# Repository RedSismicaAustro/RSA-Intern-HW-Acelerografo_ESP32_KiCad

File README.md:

# 🚀 Rediseño y Estandarización de PCB Acelerográfica en KiCad 10 (PCBA JLCPCB)

Este repositorio contiene el espacio de trabajo, documentación de referencia y material de apoyo para el desarrollo de la pasantía de **Joel Suárez** en la **Red Sísmica del Austro (RSA)**.

El objetivo central es capturar, auditar, optimizar y estandarizar el diseño del **Sistema Acelerográfico con ESP32 (SMD)** en el entorno **KiCad 10**, garantizando que el diseño sea 100% compatible con el firmware de adquisición original y esté preparado para ensamblaje automático (**PCBA**) en **JLCPCB**.

---

## 📂 Organización del Repositorio

Para mantener el flujo de trabajo simple y ordenado, el proyecto está estructurado en tres carpetas:

```text
RSA-Intern-HW-Acelerografo_ESP32_KiCad/
│
├── .gitignore                                 # Configurado para ignorar temporales y respaldos de KiCad
├── README.md                                  # Guía operativa e instrucciones de trabajo
│
├── docs/                                      # Documentación técnica de apoyo y planificación
│   ├── Planificacion_Migracion_EAGLE_KiCad.pdf # Plan de trabajo oficial detallado (96 horas)
│   └── especificacion_hardware_original.md    # Detalle de circuitos integrados, valores pasivos y pines
│
├── eagle/                                     # Material de referencia del diseño previo
│   ├── BOM_Assembly.txt                       # Lista de materiales (BOM) con valores, referencias y encapsulados
│   ├── images_schematic/                      # Capturas de los esquemas por bloques (Páginas 1 a 7 y Full)
│   └── images_pcb_3d_view/                    # Vistas 3D de referencia de la placa previa
│
└── kicad/                                     # 👉 Espacio de trabajo exclusivo para el nuevo proyecto KiCad 10
```

---

## 🧭 Metodología de Trabajo y Fases (96 horas)

Dado que el diseño previo proviene de una versión en Autodesk Fusion Electronics / EAGLE sin archivos de proyecto nativos disponibles, el trabajo se desarrollará directamente en **KiCad 10** en la carpeta [`kicad/`](./kicad) siguiendo estas 6 fases:

### 1. Captura de Esquemático y Auditoría de Pines (Pinout Audit - 16 h)
* **Captura en KiCad 10:** Crear el proyecto en [`kicad/`](./kicad) y dibujar los bloques esquemáticos utilizando como referencia las capturas en [`eagle/images_schematic/`](./eagle/images_schematic), la lista de materiales en [`eagle/BOM_Assembly.txt`](./eagle/BOM_Assembly.txt) y la [`especificacion_hardware_original.md`](./docs/especificacion_hardware_original.md).
* **Auditoría estricta contra Firmware:** Cotejar pin a pin la asignación de GPIOs del ESP32 con el código fuente del firmware de adquisición disponible en [RSA Sensor (GitHub)](https://github.com/JorgeZh-hub/RSA_sensor):
  * **ADXL355Z (SPI):** `MOSI`, `MISO`, `SCK`, `CS`.
  * **Tarjeta MicroSD (SPI + Buffer 74LVC125A):** `MOSI`, `MISO`, `SCK`, `CS`.
  * **GPS (UART):** `TX`, `RX`.
  * **RTC DS3231 (I2C + SQW):** `SDA`, `SCL`, interrupción `SQW` (1 Hz).
  * **Conversor USB/Serial (UART):** `TXD0`, `RXD0`, `DTR`, `RTS` hacia el CH340G.

### 2. Estandarización de Componentes y Códigos LCSC (16 h)
* Asignar a cada símbolo el campo de metadatos `LCSC` con el número de parte (*LCSC Part Number*) del catálogo de JLCPCB.
* Priorizar componentes clasificados como **Basic Parts** de JLCPCB para reducir costos de montaje.
* Seleccionar encapsulados SMD estándar adecuados (0805, 0603, 1206, SOT-23, SOIC).

### 3. Gestión de Librerías Locales Relativas (12 h)
* Utilizar la herramienta `jlc2kicadlib` para descargar componentes específicos que no estén en la librería oficial de KiCad.
* Alojar todos los símbolos (`.kicad_sym`), huellas (`.kicad_mod` en carpeta `.pretty`) y modelos 3D (`.step`) dentro de carpetas locales del proyecto (ej. `kicad/libs/`).
* Configurar las rutas mediante variables relativas del entorno KiCad (ej. `${KIPRJMOD}`) para que el repositorio sea **100% portable y autónomo** al clonarse en cualquier computador.

### 4. Layout Físico, Integridad y Optimización (24 h)
* **Desacoplo:** Ubicar condensadores de desacoplo (0.1 µF y 10 µF) lo más próximos posible a los pines `VCC`/`VDD` del ESP32, ADXL355 y RTC.
* **Plano de Masa:** Implementar planos de tierra robustos de cobre (GND) en ambas capas (Top y Bottom).
* **Señales Críticas:** Rutar con trazas cortas y directas las líneas de datos SPI del acelerómetro y MicroSD, minimizando el número de vías.
* **Test Points:** Incluir puntos de prueba accesibles (pads/headers) para señales críticas (`3.3V`, `5V`, `GND`, `TX/RX`, `SQW 1Hz`, bus SPI).
* **Pick & Place:** Colocar al menos 3 marcas fiduciarias (*Fiducials*) en las esquinas de la PCB.
* **DRC:** Ejecutar el Design Rules Check de KiCad y asegurar 0 errores/advertencias.

### 5. Generación y Validación de Archivos de Fabricación (14 h)
* Instalar y utilizar el plugin **Fabrication Toolkit** en KiCad para generar automáticamente el paquete PCBA:
  * Archivos Gerber y NC Drill.
  * Lista de Materiales (`BOM.csv`).
  * Archivo de Posición y Coordenadas (`CPL.csv`).
* Cargar el paquete en el visor web de JLCPCB para auditar y corregir rotaciones u offsets de los componentes SMD.

### 6. Cierre y Documentación (14 h)
* Documentar las decisiones técnicas y optimizaciones realizadas (planos GND, desacoplo, corrección de pines).
* Generar las instrucciones de actualización y exportación en el README final del proyecto.

---

## 🏆 Criterios de Éxito y Entregables Finales

1. **Proyecto KiCad 10 Funcional y Portable:** Esquemático y PCB completos en `kicad/` con librerías locales relativas.
2. **Paquete de Fabricación JLCPCB Validado:** Gerbers, BOM y CPL listos para producción sin requerir correcciones manuales en el visor de JLCPCB.
3. **Auditoría de Pines Verificada:** Informe que certifique la compatibilidad total del pinout con el firmware de adquisición.

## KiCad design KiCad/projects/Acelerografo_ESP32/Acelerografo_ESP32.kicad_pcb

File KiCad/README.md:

# Documentación técnica del PCB acelerográfico ESP32

**Proyecto:** Rediseño y estandarización del sistema acelerográfico de la Red Sísmica del Austro (RSA).  
**Responsable del trabajo según README:** Joel Suárez.  
**Entorno de diseño:** KiCad 10.  
**Fecha de revisión documental:** 7 de octubre de 2026.  
**Estado:** documentación del diseño y paquete exportado; pendiente de certificación eléctrica, de reglas y de ensamblaje.

## 1. Introducción y organización del proyecto

Este documento describe el entorno desarrollado para el PCB acelerográfico ESP32: proyecto KiCad, alimentación, bloques funcionales, bibliotecas locales, selección de componentes y preparación de archivos para fabricación PCBA. La estructura documental toma como referencia el README del Concentrador aportado, adaptando su organización al acelerógrafo. Los componentes, el origen EAGLE/Fusion del diseño y las rutas corresponden al proyecto acelerográfico; no se trasladan los datos del circuito Concentrador.

Las fuentes técnicas son el BOM `Acelerografo_ESP32.csv`, los archivos locales KiCad y las capturas proporcionadas. La organización del repositorio corresponde al árbol de carpetas aportado:

```text
RSA-Intern-HW-Acelerografo_ESP32_KiCad/
├── docs/
├── eagle_Images/
│   ├── images_pcb_3d_view/
│   └── images_schematic/
└── KiCad/
    ├── fabrication/
    ├── libs/
    │   ├── footprint/
    │   ├── JLC2KiCad_lib/
    │   │   └── RSA.pretty/
    │   │       └── packages3d/
    │   ├── LibExt.pretty/
    │   │   └── packages3d/
    │   ├── RSA.pretty/
    │   │   └── packages3d/
    │   └── symbol/
    └── projects/
        └── Acelerografo_ESP32/
            ├── .history/
            ├── production/
            └── _restore_backup_2026-09-14T22-53-35-565/
```

| Directorio | Función en el entorno |
|---|---|
| `docs/` | Documentación técnica del proyecto. |
| `eagle_Images/` | Capturas del esquemático y vistas 3D del diseño de referencia. |
| `KiCad/fabrication/` | Directorio disponible para organizar recursos de fabricación; no se encontraron archivos durante esta revisión. |
| `KiCad/libs/` | Símbolos, huellas y modelos 3D locales. |
| `KiCad/libs/JLC2KiCad_lib/` | Recursos adicionales generados por la herramienta de importación de componentes. |
| `KiCad/projects/Acelerografo_ESP32/` | Proyecto activo: `.kicad_pro`, `.kicad_sch`, `.kicad_pcb`, BOM y tablas de bibliotecas. |
| `KiCad/projects/Acelerografo_ESP32/production/` | Paquete de fabricación exportado mediante Fabrication Toolkit. |
| `.history/` y `_restore_backup_2026-09-14T22-53-35-565/` | Historial y respaldo del proyecto; no constituyen el paquete destinado al fabricante. |

El directorio `KiCad/fabrication/` y la carpeta `production/` del proyecto son ubicaciones diferentes. Los archivos exportados inspeccionados se encuentran en la segunda.
La revisión incluyó las tablas de bibliotecas, las opciones de Fabrication Toolkit, los CSV de producción y el inventario interno del ZIP de Gerbers. No se ejecutaron ERC ni DRC, no se realizó una auditoría completa de las conexiones, no se inspeccionaron gráficamente los Gerbers ni se cargó el paquete en JLCPCB. Tampoco se comprobó el firmware ni la correspondencia comercial de cada LCSC con su encapsulado. Las instrucciones de validación de este documento son pasos pendientes, no resultados aprobados.

## 2. Objetivo del proyecto

Reconstruir, auditar y estandarizar en KiCad 10 el sistema acelerográfico con ESP32 originalmente desarrollado en Autodesk Fusion Electronics/EAGLE, empleando las capturas y documentación disponibles como referencia. La placa integra adquisición de aceleración, almacenamiento local y referencias temporales, y busca mantener la compatibilidad con el firmware original.

El objetivo de fabricación es obtener un proyecto mantenible y portable, con componentes identificados mediante códigos LCSC para el ensamblaje PCBA en JLCPCB y una lista explícita de módulos y conectores instalados manualmente. La compatibilidad con el firmware y la aptitud para fabricación requieren las verificaciones eléctricas y de ensamblaje descritas en este documento.

## 3. Arquitectura general

```text
Entrada 12 V (12V1)
        │
        ▼
Módulo MP2307 (U8, montaje manual)
        │ 5 V
        ▼
LD1117S33 (U4)
        │ 3.3 V / alimentación digital prevista
        ▼
ESP32-WROOM-32 (U1)
        ├── SPI ── ADXL355Z (U3): adquisición acelerográfica
        ├── SPI ── 74LVC125 (U7) / MicroSD1: almacenamiento
        ├── UART ─ GPS1: referencia temporal y posicionamiento
        ├── I²C / SQW ─ RTC (U2) / BT1: reloj y respaldo
        └── UART ─ CH340G (U6) / USB-C (J7): comunicación/programación
```

El diagrama sintetiza la arquitectura prevista en el README y la solicitud de diseño; no reemplaza la auditoría pin a pin. El archivo PCB declara dos capas de cobre, `F.Cu` y `B.Cu`, y un espesor nominal de 1,6 mm. Estos son parámetros del diseño, no una confirmación de fabricación.

### 3.1 Alimentación 12 V → 5 V → 3,3 V

La etapa de reducción de 12 V a 5 V se implementa con un **módulo MP2307**, representado por U8. El CSV conserva el nombre genérico `STEP_DOWN_CONVERTER`; la identificación MP2307 procede de la definición del proyecto aportada por el usuario. La vista 3D muestra una pequeña placa convertidora completa en la zona superior izquierda, con inductor y elementos de regulación propios.

El módulo sustituye la implementación discreta de la etapa conmutada y se instala manualmente. La placa principal conserva condensadores externos: C20 de 220 µF y C21 de 100 nF en la zona de entrada, y C22 de 100 µF, C23 de 100 nF y C24 de 10 nF en la zona del convertidor. Su conexión exacta debe confirmarse en el esquemático; la lista de valores no certifica por sí sola su función eléctrica.

U4, `LD1117S33TR_SOT223`, realiza la regulación prevista de 5 V a 3,3 V. Su footprint es `SOT-223-3_TabPin2` y su código LCSC es C35879. Antes de conectar la electrónica digital, medir la salida del módulo a 5 V y la salida de U4 a 3,3 V; verificar pinout, polaridad, tensión admisible de condensadores, demanda máxima de corriente y disipación térmica. Documentar también el comportamiento con alimentación USB y externa simultánea mediante la revisión de las conexiones reales.

### 3.2 Bloques visibles en la captura

| Bloque | Referencias principales | Descripción y evidencia visual |
|---|---|---|
| Entrada y regulación | 12V1, U8, U4, C20–C24 | Conector de entrada arriba a la derecha, convertidor arriba a la izquierda y regulador U4 en la zona superior. |
| Control y comunicaciones | U1 | Módulo ESP32-WROOM-32 en el borde inferior derecho, con antena hacia el exterior. Revisar keepout en ambas capas. |
| Adquisición | U3 | Huella de la placa ADXL355Z en el lateral derecho, sobre el ESP32; la ausencia de cuerpo 3D no demuestra ausencia de montaje. |
| GPS | GPS1 | Área de breakout GPS en la zona superior derecha, rotulada con PA6H y su contorno mecánico. |
| Almacenamiento | MicroSD1, U7 | Portatarjetas en el lateral izquierdo inferior y buffer próximo a él. |
| Reloj y respaldo | U2, BT1 | RTC en la zona inferior central y huella del soporte de batería en la esquina inferior izquierda. |
| USB/serial | J7, U6 | USB-C en el borde izquierdo y CH340G en la zona central izquierda. |
| Control e indicación | EN1, RTS1, D3, D4 | Dos pulsadores centrales y LEDs distribuidos en la placa. |
| Interconexión y pasivos | J6, J9, J13, J16, J17, J18; R, C, D | Headers, acceso a señales, resistencias, condensadores y diodos según el BOM. |

La captura permite describir placement y presencia de huellas, pero no demuestra continuidad de planos GND, integridad de señales, cumplimiento de reglas ni montaje real. No se asigna aquí una función específica a cada diodo o resistencia sin auditar su red.

### 3.3 PCB final — vista 3D

**Figura: PCB final presentado por el usuario.** La vista muestra la distribución de la etapa de alimentación, el ESP32, los espacios para GPS y ADXL355, el puerto USB-C, el portatarjetas MicroSD y el RTC con soporte de batería. La imagen documenta la disposición física final mostrada; no representa una fotografía de una placa fabricada ni certifica ERC, DRC o validación en JLCPCB.
## 4. Librerías locales y portabilidad

La captura y `fp-lib-table` muestran dos bibliotecas de huellas específicas del proyecto:

| Apodo en KiCad | Directorio local | Uso identificado en el BOM |
|---|---|---|
| LibsExt | `KiCad/libs/LibExt.pretty` | Soporte CR1220, GPS_BREAKOUT_V3, MicroSD_holder, ADXL355Z y STEP_DOWN_CONVERTER. |
| LibsRSA | `KiCad/libs/RSA.pretty` | Huellas SMA para ES1D y TSSOP-14 para 74LVC125. |

`LibsExt` es el apodo; `LibExt.pretty` es el nombre real del directorio. No deben confundirse. Existen símbolos en `KiCad/libs/symbol/`, un archivo `KiCad/libs/RSA.kicad_sym` y modelos en subdirectorios `packages3d` de las bibliotecas.

**Estado observado:** las tablas aún utilizan rutas absolutas `C:/Users/Suarezc1224/Desktop/...`. Por tanto, la portabilidad no está completada. Además, `sym-lib-table` apunta a directorios para LibsExt y LibsRSA, en lugar de identificar archivos `.kicad_sym`; esta configuración requiere revisión y prueba de resolución de símbolos.

Como el proyecto reside en `KiCad/projects/Acelerografo_ESP32/`, las rutas relativas propuestas son:

```text
LibsExt (huellas): ${KIPRJMOD}/../../libs/LibExt.pretty
LibsRSA (huellas): ${KIPRJMOD}/../../libs/RSA.pretty
LibsRSA (símbolos, si se adopta RSA.kicad_sym): ${KIPRJMOD}/../../libs/RSA.kicad_sym
Modelo 3D local, ejemplo: ${KIPRJMOD}/../../libs/LibExt.pretty/packages3d/Convertidor STEP DOWN.step
```

Para los símbolos externos, registrar cada archivo `.kicad_sym` con el apodo correspondiente, o consolidarlos en una biblioteca válida y actualizar sus identificadores. No apuntar una biblioteca de símbolos KiCad a una carpeta como sustituto de un archivo. Mantener los apodos utilizados por los componentes o reasignarlos de forma coherente.

Después de ajustar las rutas, abrir una copia del repositorio en una ubicación distinta, comprobar símbolos, huellas y vista 3D, y revisar que no queden rutas personales. Los modelos oficiales que usan `${KICAD10_3DMODEL_DIR}` requieren las bibliotecas estándar correspondientes en el equipo receptor. Estas correcciones se documentan como propuestas; no se modificaron los archivos del proyecto durante esta tarea.

## 5. Flujo técnico del entorno desarrollado

El entorno reúne el proyecto KiCad, las bibliotecas locales, el BOM y los archivos de fabricación. Su organización permite mantener la relación entre el circuito, los componentes físicos y el paquete destinado a producción.

1. **Esquemático:** el archivo `Acelerografo_ESP32.kicad_sch` contiene la representación del circuito. Desde el editor se gestionan referencias, valores, conexiones y asignación de huellas.
2. **Bibliotecas:** `KiCad/libs/` reúne símbolos, huellas y modelos 3D. Las tablas del proyecto registran LibsExt y LibsRSA; las rutas relativas propuestas en la sección anterior facilitan trasladar el entorno a otro equipo.
3. **Componentes:** el campo LCSC identifica las piezas previstas para PCBA. Los módulos y conectores de montaje manual se mantienen en la BOM completa, separados del conjunto que se enviará a ensamblaje.
4. **PCB:** `Acelerografo_ESP32.kicad_pcb` contiene la distribución física y el ruteo. La captura 3D permite identificar los bloques y su disposición en la placa.
5. **Exportación:** Fabrication Toolkit genera el paquete en `production/`, con Gerbers, taladros, BOM y posiciones de componentes.
6. **Actualización:** después de cambiar el circuito o el layout, actualizar el PCB desde el esquemático, ejecutar las comprobaciones técnicas y regenerar el paquete para mantener los archivos de fabricación coherentes con el diseño.

Se confirmó la existencia de estos recursos. La revisión documental no incluyó la ejecución de las comprobaciones eléctricas ni la modificación de los archivos KiCad.
### 5.1 Configuración del entorno de trabajo

Abrir `KiCad/projects/Acelerografo_ESP32/Acelerografo_ESP32.kicad_pro` con KiCad 10. Mantener las bibliotecas estándar utilizadas por los footprints del BOM y registrar las bibliotecas locales en las tablas específicas del proyecto. Revisar la resolución de símbolos, huellas y modelos antes de actualizar el circuito.

Para la importación de componentes, disponer de Python y JLC2KiCadLib. Si se utiliza un entorno virtual, puede prepararse desde la raíz del repositorio:

```powershell
python -m venv .venv
.\.venv\Scripts\Activate.ps1
python -m pip install JLC2KiCadLib
jlc2kicadlib --help
```

Estos comandos describen la preparación del entorno y no se ejecutaron en esta revisión. La versión de Python debe ser compatible con la versión instalada de la herramienta; no se presupone que el entorno del Concentrador sea idéntico al del acelerógrafo.

El entorno incluye Fabrication Toolkit para exportar el paquete desde el editor PCB. Si se prepara otro equipo, instalar el complemento desde el administrador de complementos y contenidos de KiCad y comprobar que esté disponible en el editor.

### 5.2 Campos de componentes y mantenimiento

Mantener `Reference`, `Value`, `Footprint` y `LCSC` coherentes entre esquemático, PCB y exportación. `Qty` es la cantidad agrupada en el BOM. Los campos Datasheet, Description, fabricante y número de parte pueden complementar la identificación sin sustituir el LCSC ni el encapsulado real.

Los elementos manuales conservan su huella en la placa. Para excluirlos de los archivos de ensamblaje, revisar sus atributos de BOM y de posición según la configuración mostrada en la sección de fabricación. Mantener una BOM completa independiente para documentar tanto las piezas PCBA como las de instalación posterior.

Las bibliotecas compartidas se deben actualizar de forma controlada; después de cambiar una huella, comprobar pads, numeración, posición y modelo 3D. Mantener las modificaciones locales versionadas junto al proyecto.
## 6. Lista completa de componentes

La tabla se transcribe del CSV aportado sin sustituir valores ni footprints. Hay **32 filas agrupadas, 59 componentes físicos, 22 códigos LCSC únicos**, con **47 componentes previstos para JLCPCB** y **12 para montaje manual**. `—` representa una celda originalmente vacía. MicroSD1 tiene el campo Value vacío en el CSV.

Un código LCSC indica selección de catálogo y destino de ensamblaje previsto; no certifica stock, categoría Basic/Extended, compatibilidad de footprint ni aceptación del pedido.

### 6.1 Componentes con LCSC — ensamblaje JLCPCB previsto

| Reference | Qty | Value | Footprint | LCSC |
|---|---:|---|---|---|
| BT1 | 1 | Battery | LibsExt:CR1220-2-ext | C70381 |
| C8,C16 | 2 | 10uF | Capacitor_SMD:CP_Elec_4x5.4 | C3343 |
| C9 | 1 | 200nF | Capacitor_SMD:C_0805_2012Metric | C344170 |
| C10,C11 | 2 | 100uF | Capacitor_SMD:CP_Elec_6.3x7.7 | C3338 |
| C12,C13,C14,C15,C17,C19,C21,C23 | 8 | 100nF | Capacitor_SMD:C_0402_1005Metric | C1525 |
| C18 | 1 | 1uF | Capacitor_SMD:C_0402_1005Metric | C29266 |
| C20 | 1 | 220uF | Capacitor_SMD:CP_Elec_4x5.4 | C2858857 |
| C22 | 1 | 100uF | Capacitor_SMD:CP_Elec_4x5.4 | C970695 |
| C24 | 1 | 10nF | Capacitor_SMD:C_0402_1005Metric | C15195 |
| D1,D2,D5,D6,D7 | 5 | ES1D | LibsRSA:SMA_L4.4-W2.8-LS5.4-RD | C64878 |
| D3,D4 | 2 | LED | LED_SMD:LED_0603_1608Metric | C2290 |
| EN1,RTS1 | 2 | SW_Push | Button_Switch_SMD:SW_SPST_EVQPE1 | C720477 |
| MicroSD1 | 1 | — | LibsExt:MicroSD_holder | C53223918 |
| R4,R6,R14,R15,R16,R17 | 6 | 4.7k | Resistor_SMD:R_1206_3216Metric | C17936 |
| R5,R9 | 2 | 10k | Resistor_SMD:R_1206_3216Metric | C17902 |
| R7,R8 | 2 | 5.1k | Resistor_SMD:R_0805_2012Metric | C27834 |
| R10,R11,R12,R13 | 4 | 3.3k | Resistor_SMD:R_1206_3216Metric | C26010 |
| R18 | 1 | 200 | Resistor_SMD:R_0805_2012Metric | C17540 |
| U2 | 1 | DS3231M | Package_SO:SOIC-16W_7.5x10.3mm_P1.27mm | C9866 |
| U4 | 1 | LD1117S33TR_SOT223 | Package_TO_SOT_SMD:SOT-223-3_TabPin2 | C35879 |
| U6 | 1 | CH340G | Package_SO:SOIC-16_3.9x9.9mm_P1.27mm | C14267 |
| U7 | 1 | 74LVC125 | LibsRSA:TSSOP-14_L5.0-W4.4-P0.65-LS6.4-BL | C7813 |

### 6.2 Componentes sin LCSC — montaje manual / DNP-PCBA

Los campos LCSC vacíos son intencionales: estos módulos, conectores y elementos externos se excluyen del ensamblaje JLCPCB y se instalan posteriormente. DNP-PCBA significa que no se montan en fábrica, aunque sí forman parte del producto terminado. MicroSD1 y BT1 pertenecen a la tabla anterior porque tienen LCSC; no se excluyen por su categoría física.

| Reference | Qty | Value | Footprint | LCSC |
|---|---:|---|---|---|
| 12V1 | 1 | Conn_01x02 | Connector:JWT_A3963_1x02_P3.96mm_Vertical | — |
| GPS1 | 1 | GPS_BREAKOUT_V3 | LibsExt:GPS_BREAKOUT_V3 | — |
| J6 | 1 | Conn_01x04_Pin | Connector_PinHeader_2.54mm:PinHeader_1x04_P2.54mm_Vertical | — |
| J7 | 1 | USB_C_Receptacle | Connector_USB:USB_C_Receptacle_Amphenol_12401610E4-2A | — |
| J9 | 1 | IN_LD | Connector_PinHeader_2.54mm:PinHeader_1x01_P2.54mm_Vertical | — |
| J13,J16 | 2 | Conn_01x01_Pin | Connector_PinHeader_2.54mm:PinHeader_1x01_P2.54mm_Vertical | — |
| J17,J18 | 2 | Conn_01x05_Pin | Connector_PinHeader_2.54mm:PinHeader_1x05_P2.54mm_Vertical | — |
| U1 | 1 | ESP32-WROOM-32 | RF_Module:ESP32-WROOM-32 | — |
| U3 | 1 | ADXL355Z | LibsExt:ADXL355Z | — |
| U8 | 1 | STEP_DOWN_CONVERTER | LibsExt:STEP_DOWN_CONVERTER | — |

## 7. Importación con jlc2kicadlib

El siguiente comando PowerShell incluye exactamente los 22 códigos únicos del BOM, conservando el orden de primera aparición y los parámetros solicitados. Documenta una operación reproducible; no se ejecutó durante la generación de este informe.

```powershell
jlc2kicadlib `
C70381 C3343 C344170 C3338 C1525 C29266 C2858857 C970695 C15195 C64878 C2290 C720477 C53223918 C17936 C17902 C27834 C26010 C17540 C9866 C35879 C14267 C7813 `
-dir "C:\Users\Suarezc1224\Desktop\RSA-Intern-HW-Acelerografo_ESP32_KiCad\KiCad\libs" `
-symbol_lib RSA `
-symbol_lib_dir . `
-footprint_lib RSA.pretty `
-model_dir packages3d `
--skip_existing
```

Ejecutar en PowerShell con la herramienta instalada y sin espacios después de los acentos graves de continuación. Si cambia la ubicación del repositorio, ajustar `-dir`. Conservar `--skip_existing` y revisar el registro de importación; no asumir que actualiza o corrige componentes ya presentes. La descarga no sustituye la revisión de pinout, pads, orientación y dimensiones. Confirmar las rutas generadas de los modelos 3D y registrar las bibliotecas resultantes bajo los apodos del proyecto.

## 8. Carpeta production y Fabrication Toolkit

La carpeta `KiCad/projects/Acelerografo_ESP32/production/` contiene el paquete generado mediante **Fabrication Toolkit**, según el flujo descrito por el usuario y la presencia de sus opciones de exportación. **Sí se inspeccionó su contenido real a nivel de listado, CSV y entradas del ZIP.** No se realizó una inspección gráfica ni una validación de fabricación.

Los nombres genéricos `BOM.csv` y `CPL.csv` describen los entregables de materiales y posiciones; los archivos existentes usan los nombres siguientes:

| Archivo real | Función |
|---|---|
| `JLPCB_Acele-ESP32.zip` | Paquete de Gerbers y NC Drill. |
| `JLPCB_Acele-ESP32_bom.csv` | Equivalente funcional a BOM.csv: referencias, footprint, cantidad, valor y LCSC. |
| `JLPCB_Acele-ESP32_positions.csv` | Equivalente funcional a CPL.csv: Designator, Mid X, Mid Y, Rotation y Layer. |
| `JLPCB_Acele-ESP32_designators.csv` | Archivo auxiliar de designadores; se confirmó su presencia, sin evaluar su contenido. |
| `netlist.ipc` | Netlist auxiliar; se confirmó su presencia, sin validar conectividad. |

Dentro del ZIP se encontraron:

```text
Acelerografo_ESP32-F_Cu.gtl
Acelerografo_ESP32-B_Cu.gbl
Acelerografo_ESP32-F_Mask.gts
Acelerografo_ESP32-B_Mask.gbs
Acelerografo_ESP32-F_Paste.gtp
Acelerografo_ESP32-B_Paste.gbp
Acelerografo_ESP32-F_Silkscreen.gto
Acelerografo_ESP32-B_Silkscreen.gbo
Acelerografo_ESP32-Edge_Cuts.gm1
Acelerografo_ESP32-PTH.drl
Acelerografo_ESP32-NPTH.drl
Acelerografo_ESP32-PTH-drl_map.gbr
Acelerografo_ESP32-NPTH-drl_map.gbr
```

Los archivos `.drl` corresponden a taladros metalizados (PTH) y no metalizados (NPTH); los mapas asociados apoyan su revisión. No hay archivos literalmente llamados `BOM.csv` o `CPL.csv` en el listado revisado: deben seleccionarse sus equivalentes al cargar el pedido.

### 8.1 Configuración de exclusión y exportación mostrada

En las propiedades del componente, la captura aportada muestra activados **Excluir de la lista de materiales** y **Excluir de los archivos de posición**. **Excluir de la placa** permanece desactivado: el componente conserva su lugar físico en el PCB para el montaje manual.

Esta captura ilustra los atributos de un elemento; no demuestra por sí sola que se hayan aplicado a todas las referencias manuales. La exclusión de BOM y posición debe comprobarse para cada elemento de ese grupo. No equivale automáticamente a marcar DNP.

En Fabrication Toolkit se muestra el nombre de exportación **Acelerografo_V1_RevA** y las siguientes opciones:

| Opción | Estado visible |
|---|---|
| Apply automatic component translations | Activada. |
| Apply automatic fill for all zones | Activada. |
| Exclude DNP components from BOM | Activada. |
| Open browser after generation | Activada. |
| Generate backup files | Activada. |
| Plot all active layers | Desactivada. |
| Set User.1 as V-Cut layer | Desactivada. |
| Set User.2 as alternative Edge-Cut layer | Desactivada. |

Después de revisar los atributos y guardar el diseño, ejecutar **Generate**, comprobar el directorio de salida y revisar el contenido del BOM y del CPL. Conservar junto al paquete la revisión del proyecto de la que se exportó.

**Diferencia entre la captura y los archivos inspeccionados:** la nueva captura muestra exclusión DNP activada y el nombre `Acelerografo_V1_RevA`. El archivo de opciones todavía disponible en disco conserva `EXCLUDE DNP: false` y `ARCHIVE_NAME: JLPCB Acele-ESP32`; los archivos encontrados en `production/` usan el prefijo `JLPCB_Acele-ESP32`. Por tanto, la captura documenta la configuración presentada, pero no confirma que el paquete existente se haya regenerado con ella. No se encontró un paquete con el nombre nuevo en el listado revisado.

### 8.2 Observaciones del paquete existente en disco

- El BOM de producción todavía contiene las 32 filas, incluidos los componentes manuales sin LCSC. La opción `EXCLUDE DNP` figura como `false` en `fabrication-toolkit-options.json`. Los campos LCSC vacíos no prueban por sí solos que estos componentes se excluirán del pedido.
- El archivo de posiciones tiene 56 referencias, todas en `top`; incluye componentes de montaje manual. GPS1, U3 y U8 no aparecen en ese archivo. Para el pedido final, comprobar que BOM y CPL contengan exactamente el conjunto autorizado para PCBA.
- MicroSD1 aparece como `MICROSD1` en los archivos de producción y con valor `~`. Normalizar/verificar referencias y completar su descripción en el flujo de pedido sin confundir el marcador con una especificación comercial.
- Debe verificarse cada combinación LCSC/Value/Footprint contra la ficha del fabricante y la selección de JLCPCB. Esta revisión no certifica, por ejemplo, la correspondencia del nombre `DS3231M` con el encapsulado SOIC-16W indicado en el BOM.

Para obtener el paquete definitivo, marcar los componentes manuales como excluidos de PCBA mediante los atributos admitidos por la versión instalada del plugin, activar la exclusión aplicable y regenerar. Alternativamente, preparar BOM y CPL filtrados coherentemente para ensamblaje, conservando por separado la BOM completa. Confirmar el resultado exportado; no basta con cambiar una opción. No se modificó el paquete original durante esta tarea.

## 9. ERC y auditoría eléctrica

1. Abrir el proyecto y resolver las bibliotecas de símbolos antes de revisar el circuito.
2. Ejecutar ERC desde el editor de esquemáticos y registrar fecha, versión, errores y advertencias.
3. Revisar alimentación, pines sin conexión, nombres de red, salidas enfrentadas, entradas flotantes y pines de potencia. Utilizar marcas de no conexión y PWR_FLAG solo cuando el circuito lo justifique.
4. Auditar la cadena 12 V → módulo MP2307 → 5 V → LD1117S33 → 3,3 V, pinout del módulo, masas, polaridad y protección. Comprobar interacción entre USB y fuente externa.
5. Comparar con el firmware GPIO de ADXL355 y MicroSD por SPI, GPS por UART, RTC por I²C/SQW y CH340G por UART/DTR/RTS. Registrar una tabla de señal, GPIO, pin físico y evidencia de firmware.
6. Corregir incidencias y repetir ERC; justificar cualquier exclusión de forma individual. Actualizar el PCB desde el esquemático.

**Resultado de ERC en esta revisión: no ejecutado.** No se declara cero errores ni compatibilidad de firmware verificada.

## 10. DRC y revisión física

1. Seleccionar las reglas de fabricación del servicio y stackup que se contratarán: separación, anchos, vías, taladros y distancias a bordes.
2. Rellenar zonas de cobre y ejecutar DRC en el editor PCB; revisar conexiones sin rutear, cortocircuitos, separaciones, taladros, contorno y courtyards.
3. Revisar continuidad y retornos de GND en ambas capas, desacoplos cercanos a los pines, longitud de SPI y ubicación del acelerómetro respecto de la etapa conmutada.
4. Comprobar keepout de antena ESP32, interferencias mecánicas, acceso a USB/MicroSD, altura de módulos, polaridad y pin 1. Revisar los puntos de prueba y la disposición de fiduciales para el ensamblaje.
5. Resolver errores y advertencias o registrar la justificación técnica de cada excepción.
6. Guardar la revisión aprobada y regenerar todos los archivos de producción desde ella.

**Resultado de DRC en esta revisión: no ejecutado.** La vista 3D y el ZIP existente no acreditan cumplimiento de reglas.

## 11. Validación del pedido en JLCPCB

1. Cargar el ZIP de Gerbers y revisar capas, dimensiones, contorno, máscara, serigrafía y taladros en el visor. Confirmar dos capas y espesor previsto de 1,6 mm según el pedido elegido.
2. Elegir ensamblaje en las caras que correspondan al diseño final; la exportación actual contiene posiciones en top.
3. Cargar el BOM de PCBA y el CPL coherentes, excluyendo las 12 referencias físicas de montaje manual. Mantener su lista para la instalación posterior.
4. Verificar para cada LCSC valor, part number, fabricante, encapsulado, stock y clasificación Basic/Extended. Resolver el Value vacío de MicroSD1 y cualquier incompatibilidad detectada.
5. Revisar la vista de ensamblaje referencia por referencia: coordenadas, unidades, origen, cara, rotación, pin 1 y polaridad. No interpretar automáticamente las coordenadas Y negativas como error; comprobar su resultado en el visor.
6. Comprobar que ninguna pieza manual figure en el ensamblaje solicitado, que no falte ninguna pieza aprobada y que cantidades de BOM y CPL coincidan.
7. Archivar capturas del visor, BOM/CPL aceptados, revisión del proyecto y lista de incidencias resueltas antes de aprobar la fabricación.

**Estado de validación JLCPCB: pendiente; no se cargó ni se aprobó un pedido en esta tarea.**

## 12. Montaje manual y puesta en marcha

Tras recibir la placa ensamblada, inspeccionar soldaduras y orientación de componentes. Instalar 12V1, GPS1, J6, J7, J9, J13, J16, J17, J18, U1, U3 y U8 conforme al esquema y a la lista de montaje manual. Revisar especialmente el sentido de entrada/salida del convertidor y los conectores de módulos.

Antes de energizar, comprobar ausencia de cortocircuitos en las líneas de alimentación. Verificar 5 V y 3,3 V con alimentación controlada antes de conectar los módulos sensibles. Después, comprobar programación y comunicación del ESP32, lectura de los tres ejes del acelerómetro, escritura/lectura de MicroSD, comunicación GPS y funcionamiento del RTC y su respaldo. Registrar mediciones, versión de firmware y resultados.

## 13. Estado técnico de los archivos del entorno

| Elemento | Estado documental observado |
|---|---|
| Proyecto KiCad y vista 3D | Disponibles; revisión eléctrica integral pendiente. |
| BOM completa | 32 filas / 59 componentes, transcrita en este documento. |
| Separación de montaje | 47 componentes PCBA previstos / 12 manuales documentados; exclusión en exportación pendiente. |
| Importación LCSC | Comando preparado con 22 códigos únicos; no ejecutado aquí. |
| Librerías locales | Presentes; rutas absolutas y entradas de símbolos por corregir/verificar. |
| Fabrication Toolkit / production | Paquete presente e inventariado; inspección gráfica y aceptación pendientes. |
| ERC / DRC | Sin resultados certificados en esta revisión. |
| Firmware y pruebas de banco | Pendientes de auditoría y evidencia. |

La liberación para fabricación requiere completar la portabilidad, auditar las partes y conexiones, cerrar ERC/DRC, regenerar BOM/CPL con exclusión coherente del montaje manual y validar el paquete en JLCPCB.

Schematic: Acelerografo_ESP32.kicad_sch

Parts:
12V1: Conn_01x02; JWT_A3963_1x02_P3.96mm_Vertical
BT1: Battery; CR1220-2-ext; LCSC C70381
C8, C16: 10uF; CP_Elec_4x5.4; LCSC C3343
C9: 200nF; C_0805_2012Metric; LCSC C344170
C10, C11: 100uF; CP_Elec_6.3x7.7; LCSC C3338
C12, C13, C14, C15, C17, C19, C21, C23: 100nF; C_0402_1005Metric; LCSC C1525
C18: 1uF; C_0402_1005Metric; LCSC C29266
C20: 220uF; CP_Elec_4x5.4; LCSC C2858857
C22: 100uF; CP_Elec_4x5.4; LCSC C970695
C24: 10nF; C_0402_1005Metric; LCSC C15195
D1, D2, D5, D6, D7: ES1D; SMA_L4.4-W2.8-LS5.4-RD; LCSC C64878
D3, D4: LED; LED_0603_1608Metric; LCSC C2290
EN1: SW_Push; SW_SPST_EVQPE1; LCSC C720477
GPS1: GPS_BREAKOUT_V3
J6: Conn_01x04_Pin; PinHeader_1x04_P2.54mm_Vertical
J7: USB_C_Receptacle; USB_C_Receptacle_Amphenol_12401610E4-2A
J9: IN_LD; PinHeader_1x01_P2.54mm_Vertical
J13, J16: Conn_01x01_Pin; PinHeader_1x01_P2.54mm_Vertical
J17, J18: Conn_01x05_Pin; PinHeader_1x05_P2.54mm_Vertical
MicroSD1: MicroSD_holder; LCSC C53223918
R4, R6, R14, R15, R16, R17: 4.7k; R_1206_3216Metric; LCSC C17936
R5, R9: 10k; R_1206_3216Metric; LCSC C17902
R7, R8: 5.1k; R_0805_2012Metric; LCSC C27834
R10, R11, R12, R13: 3.3k; R_1206_3216Metric; LCSC C26010
R18: 200; R_0805_2012Metric; LCSC C17540
RTS1: SW_Push; SW_SPST_EVQPE1; LCSC C720477
U1: ESP32-WROOM-32
U2: DS3231M; SOIC-16W_7.5x10.3mm_P1.27mm; LCSC C9866
U3: ADXL355Z
U4: LD1117S33TR_SOT223; SOT-223-3_TabPin2; LCSC C35879
U6: CH340G; SOIC-16_3.9x9.9mm_P1.27mm; LCSC C14267
U7: 74LVC125; TSSOP-14_L5.0-W4.4-P0.65-LS6.4-BL; LCSC C7813
U8: STEP_DOWN_CONVERTER

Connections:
/BATT: BT1.1 (+), D7.1 (K), U2.14 (VBAT)
/CS: J18.3, R11.1, U1.29 (IO5)
/D3-SD: MicroSD1.7 (DAT0), R13.1
/D+: J7.A6 (D+), J7.B6 (D+), U6.5 (UD+)
/D-: J7.A7 (D-), J7.B7 (D-), U6.6 (UD-)
/EN: C13.1, C17.2, D5.2 (A), EN1.1, R9.1, U1.3 (EN)
/ESP0: C14.1, D6.2 (A), RTS1.2, U1.25 (IO0)
/ESP12: J6.2, U1.14 (IO12), U3.12 (MISO/SDA)
/ESP13: J6.3, U1.16 (IO13), U3.9 (MOSI/SDA)
/ESP14: J6.1, U1.13 (IO14), U3.8 (SCLK/GND)
/ESP15: J6.4, R5.2, U1.23 (IO15), U3.7 (CS/SCL)
/MISO: J16.1 (Pin_1_1), J18.5, U1.31 (IO19), U7.11
/MOSI: J17.5, R10.1, U1.37 (IO23)
/Out0-SD: MicroSD1.3 (CMD), U7.3
/Out1-SD: MicroSD1.5 (CLK), U7.6
/Out2-SD: MicroSD1.2 (CD/DAT3), U7.8
/PWR_USB-C: D2.2 (A), J7.A4 (VBUS), J7.A9 (VBUS), J7.B4 (VBUS), J7.B9 (VBUS), R6.2
/RX-GPS: GPS1.3 (RXD), J18.2, U1.28 (IO17)
/RXD0-ESP: J17.2, U6.3 (RXD)
/SCK: J18.4, R12.1, U1.30 (IO18)
/SCL: J17.4, R16.1, U1.36 (IO22), U2.16 (SCL)
/SDA: J17.1, R17.1, U2.15 (SDA)
/TX-GPS: GPS1.4 (TXD), J18.1, U1.27 (IO16)
/TXD0-ESP: J17.3, U6.2 (TXD)
GND: 12V1.1, BT1.2 (-), C8.2, C9.2, C10.2, C11.2, C12.2, C13.2, C14.2, C15.2, C16.2, C17.1, C18.2, C19.2, C20.2, C21.2, C22.2, C23.2, C24.2, D3.1 (K), D4.1 (K), EN1.2, GPS1.2 (GND), J7.A1 (GND), J7.A12 (GND), J7.B1 (GND), J7.B12 (GND), J7.SH (SHIELD), MicroSD1.6 (GND), MicroSD1.9 (SH), R7.1, R8.1, RTS1.1, U1.1 (GND), U1.15 (GND), U1.38 (GND), U1.39 (GND), U2.5 (GND), U2.6 (GND), U2.7 (GND), U2.8 (GND), U2.9 (GND), U2.10 (GND), U2.11 (GND), U2.12 (GND), U2.13 (GND), U3.6 (GND), U4.1 (GND), U6.1 (GND), U7.1, U7.4, U7.7 (GND), U7.10, U7.13, U8.2 (IN-), U8.4 (OUT-)
unnamed: 12V1.2, C20.1, C21.1, U8.1 (IN+)
unnamed: C22.1, C23.1, C24.1, D1.2 (A), R4.1, U8.3 (OUT+)
unnamed: C8.1, C9.1, C10.1, D1.1 (K), D2.1 (K), J9.1 (Pin_1_1), U4.3 (VI)
unnamed: D3.2 (A), R4.2
unnamed: D4.2 (A), R6.1
unnamed: D5.1 (K), U6.13 (~DTR)
unnamed: D6.1 (K), U6.14 (~RTS)
unnamed: D7.2 (A), R18.2
unnamed: J7.A5 (CC1), R7.2
unnamed: J7.B5 (CC2), R8.2
unnamed: R10.2, U7.2
unnamed: R11.2, U7.9
unnamed: R12.2, U7.5
unnamed: R13.2, U7.12
unnamed: R15.2, U2.1 (32KHZ)
unnamed: R14.1, U2.3 (~INT/SQW)
VCC: C11.1, C12.1, C15.1, C16.1, C18.1, C19.1, GPS1.8 (3.3V), J13.1 (Pin_1_1), MicroSD1.4 (VDD), R5.1, R9.2, R14.2, R15.1, R16.2, R17.2, R18.1, U1.2 (VDD), U2.2 (VCC), U3.5 (VDD), U4.2 (VO), U6.4 (V3), U6.16 (VCC), U7.14 (VCC)

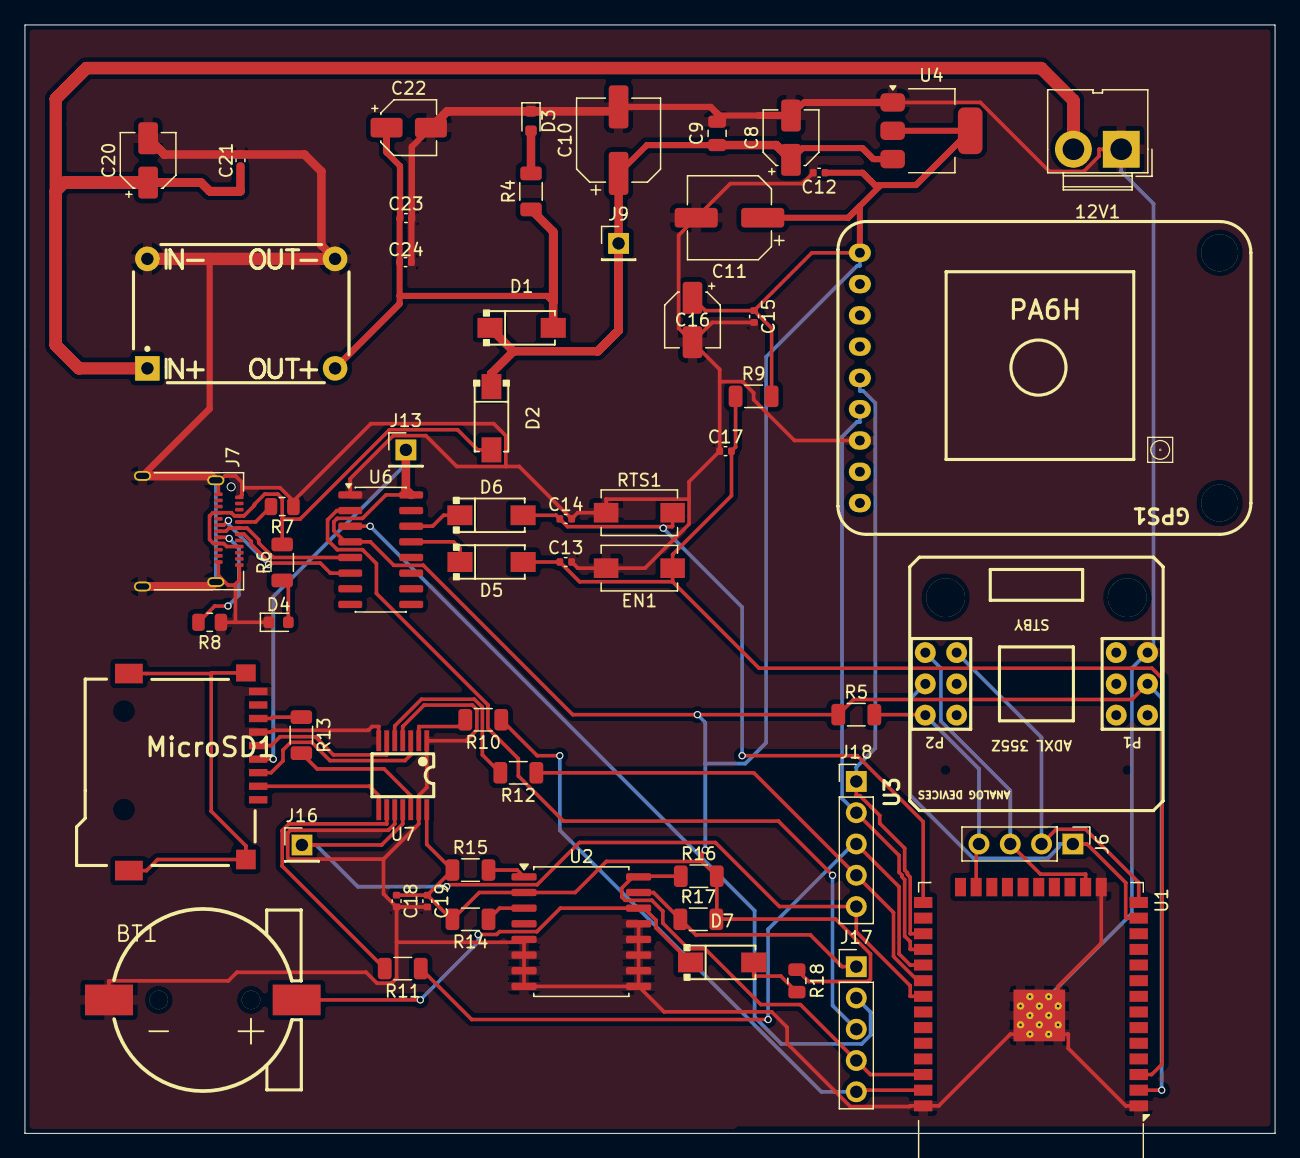
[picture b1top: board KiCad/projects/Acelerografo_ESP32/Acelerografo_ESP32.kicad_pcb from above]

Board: 2 copper layers, 101.5 x 90.0 mm, 59 parts (0 on the bottom side), 42 nets.

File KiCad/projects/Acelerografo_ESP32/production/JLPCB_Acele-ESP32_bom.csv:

Designator,Footprint,Quantity,Value,LCSC Part #
12V1,JWT_A3963_1x02_P3.96mm_Vertical,1,Conn_01x02,
BT1,CR1220-2-ext,1,Battery,C70381
"C10, C11",CP_Elec_6.3x7.7,2,100uF,C3338
"C12, C13, C14, C15, C17, C19, C21, C23",0402,8,100nF,C1525
"C16, C8",CP_Elec_4x5.4,2,10uF,C3343
C18,0402,1,1uF,C29266
C20,CP_Elec_4x5.4,1,220uF,C2858857
C22,CP_Elec_4x5.4,1,100uF,C970695
C24,0402,1,10nF,C15195
C9,0805,1,200nF,C344170
"D1, D2, D5, D6, D7",SMA_L4.4-W2.8-LS5.4-RD,5,ES1D,C64878
"D3, D4",0603,2,LED,C2290
"EN1, RTS1",SW_SPST_EVQPE1,2,SW_Push,C720477
GPS1,GPS_BREAKOUT_V3,1,GPS_BREAKOUT_V3,
"J13, J16",PinHeader_1x01_P2.54mm_Vertical,2,Conn_01x01_Pin,
"J17, J18",PinHeader_1x05_P2.54mm_Vertical,2,Conn_01x05_Pin,
J6,PinHeader_1x04_P2.54mm_Vertical,1,Conn_01x04_Pin,
J7,USB_C_Receptacle_Amphenol_12401610E4-2A,1,USB_C_Receptacle,
J9,PinHeader_1x01_P2.54mm_Vertical,1,IN_LD,
MICROSD1,MicroSD_holder,1,~,C53223918
"R10, R11, R12, R13",1206,4,3.3k,C26010
"R14, R15, R16, R17, R4, R6",1206,6,4.7k,C17936
R18,0805,1,200,C17540
"R5, R9",1206,2,10k,C17902
"R7, R8",0805,2,5.1k,C27834
U1,ESP32-WROOM-32,1,ESP32-WROOM-32,
U2,SOIC-16W_7.5x10.3mm_P1.27mm,1,DS3231M,C9866
U3,ADXL355Z,1,ADXL355Z,
U4,SOT-223-3_TabPin2,1,LD1117S33TR_SOT223,C35879
U6,SOIC-16_3.9x9.9mm_P1.27mm,1,CH340G,C14267
U7,TSSOP-14_L5.0-W4.4-P0.65-LS6.4-BL,1,74LVC125,C7813
U8,STEP_DOWN_CONVERTER,1,STEP_DOWN_CONVERTER,

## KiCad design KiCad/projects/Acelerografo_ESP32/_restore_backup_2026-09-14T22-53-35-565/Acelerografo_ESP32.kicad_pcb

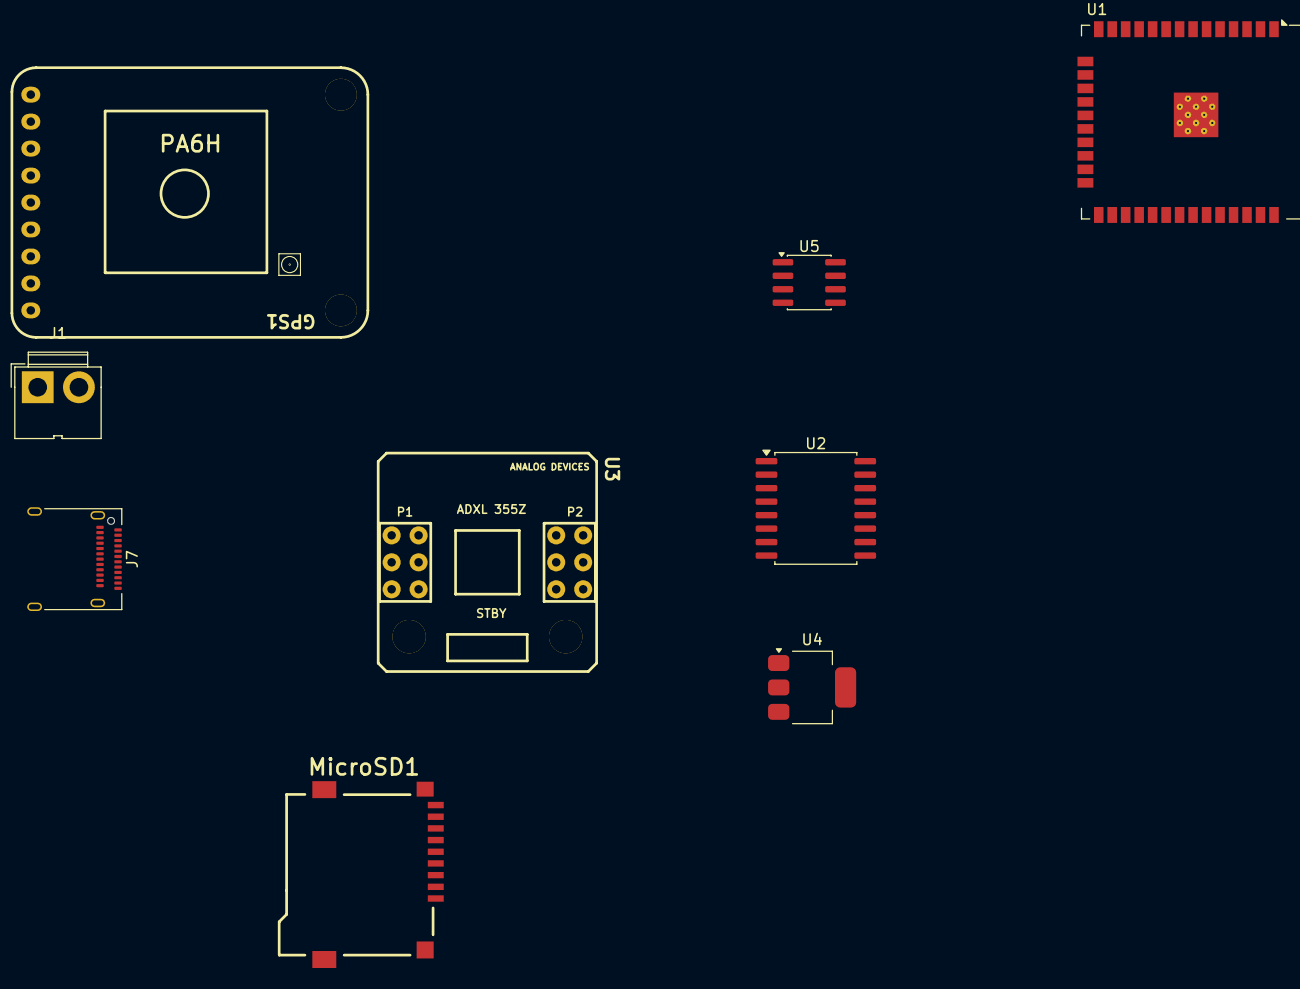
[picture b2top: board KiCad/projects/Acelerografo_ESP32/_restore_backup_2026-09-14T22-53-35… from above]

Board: 2 copper layers, 9 parts (0 on the bottom side), 7 nets, no tracks yet.

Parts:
GPS1: GPS_BREAKOUT_V3
J1: Conn_01x02; JWT_A3963_1x02_P3.96mm_Vertical
J7: USB_C_Receptacle; USB_C_Receptacle_Amphenol_12401610E4-2A
MicroSD1: MicroSD_holder
U1: ESP32-WROOM-32
U2: DS3231M; SOIC-16W_7.5x10.3mm_P1.27mm
U3: ADXL355Z
U4: LD1117S33TR_SOT223; SOT-223-3_TabPin2
U5: MP2307; SOIC-8_3.9x4.9mm_P1.27mm

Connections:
/IN_MP2307: J1.2, U5.2 (IN)
/PWR_USB-C: J7.A4 (VBUS), J7.A9 (VBUS), J7.B4 (VBUS), J7.B9 (VBUS)
GND: GPS1.2 (GND), J1.1, U3.6 (GND), U4.1 (GND), U5.4 (GND)
unnamed: J7.A1 (GND), J7.A12 (GND), J7.B1 (GND), J7.B12 (GND)
unnamed: U1.1 (GND), U1.15 (GND), U1.38 (GND), U1.39 (GND)
unnamed: U2.5 (GND), U2.6 (GND), U2.7 (GND), U2.8 (GND), U2.9 (GND), U2.10 (GND), U2.11 (GND), U2.12 (GND), U2.13 (GND)
VCC: GPS1.8 (3.3V), U3.5 (VDD), U4.2 (VO)
